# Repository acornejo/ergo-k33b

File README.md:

# ergo-k33b

A 56-key split/unified ortholinear keyboard with an integrated trackpad, designed in [Ergogen](https://ergogen.xyz/) and routed manually in KiCad.

## Overview

The ergo-k33b is a custom keyboard PCB featuring a symmetric 6×4 column-staggered matrix on each half, palm modifier keys, a 3-key thumb cluster per side, and an optional 65mm×50mm Azoteq TPS65 trackpad mounted in the center of the board.

The board uses a single unified PCB that mirrors the left and right halves — no split cable required.

## Images

### PCB — Top

### PCB — Bottom

### Front Plate

### Back Plate

### Case

## Key Layout

- **Total keys:** 56 (10 palm keys + 6 thumb keys + 40 matrix keys)
- **Matrix:** 6 columns × 4 rows per side, with column stagger:
  - Outer/pinky columns: +0/+2.5 mm stagger
  - Ring column: +5 mm stagger
  - Middle column: +2.5 mm stagger
  - Index column: −2.5 mm stagger
  - Inner column: −5 mm stagger
- **Thumb cluster:** 3 keys per side, splayed outward from the inner-bottom matrix position
- **Palm keys:** 1 key per side below the outer column, intended for modifier keys
- **Switch type:** Cherry MX (5-pin), with optional hotswap socket support

## Hardware

| Component | Part | Notes |
|---|---|---|
| MCU | [Nice!Nano](https://nicekeyboards.com/nice-nano/) (nRF52840 SuperMini) | Mounted on the back, centered between halves |
| Display | [Nice!View](https://nicekeyboards.com/nice-view/) | Optional; SPI via P1/P2/P3 |
| Trackpad | [Azoteq TPS65](https://www.azoteq.com/) (65mm × 50mm) | Optional; I²C via P4/P5, ready signal P0 |
| Switches | Cherry MX 5-pin | Hotswap and solder options |
| Diodes | SOD-123 (SMD) + THT | Both footprints populated; one per key |
| Battery connector | Molex Pico EZmate 1×2 | Also exposes BAT\_P / GND solder pads as an alternative |
| Trackpad connector | Molex Pico EZmate 1×5 | Also exposes RST / RDY / GND / VCC / SCL / SDA solder pads as an alternative |
| Power switch | SMD side-mount | On the back of the board |
| Reset button | SMD side-mount | On the back of the board |

### Connector choice

Both the battery and trackpad use [Molex Pico EZmate](https://www.molex.com/en-us/products/connectors/wire-to-board-connectors/pico-ezmate-connectors) connectors rather than the more common JST-PH standard. Pico EZmate has a lower profile (1.48 mm mated height vs. 3.0 mm for JST-PH), which keeps the overall board assembly thinner. Each connector also has corresponding solder pad footprints on the PCB, so you can wire the battery or trackpad directly without a connector if preferred.

## PCB Design

The PCB was designed using [Ergogen](https://ergogen.xyz/) v4.2 to generate the board outline, key positions, and component footprints from `ergogen/config.yaml`. Routing was done manually in KiCad. The freerouting scripts in this repo are provided for experimentation only.

Three PCBs are generated from the Ergogen config:

| PCB | Description |
|---|---|
| `main_board` | The keyboard PCB with all switches, diodes, MCU, and connectors |
| `frontplate` | Switch plate with key cutouts and screw holes |
| `backplate` | Bottom cover plate with screw holes |

A `bottom_case` 3D model (STL) is also generated from the Ergogen outlines using OpenJSCAD.

### Pinout (nRF52840 SuperMini)

| Pin | Function |
|---|---|
| P21 | Column: outer |
| P20 | Column: pinky |
| P19 | Column: ring |
| P18 | Column: middle |
| P15 | Column: index |
| P14 | Column: inner |
| P10 | Row: bottom |
| P8 | Row: home |
| P16 | Row: top |
| P7 | Row: num |
| P9 | Row: thumb cluster |
| P13 | Row: palm keys |
| P0 | Trackpad RDY |
| P4 | Trackpad SCL (I²C) |
| P5 | Trackpad SDA (I²C) |
| P6 | Trackpad RST |
| P1 | Nice!View CS |
| P2 | Nice!View MOSI |
| P3 | Nice!View SCK |

## Repository Structure

```
ergogen/
  config.yaml       # Full Ergogen board definition
output/
  pcbs/             # Generated KiCad PCB files
  cases/            # Generated OpenJSCAD and STL files
  outlines/         # Generated outline DXFs
  gerbers/          # Fabrication outputs
scripts/
  boards.kibot.yaml # KiBot config for main board exports
  default.kibot.yaml# KiBot config for plate exports
  export_dsn.py     # Export KiCad PCB to Specctra DSN
  import_ses.py     # Import Specctra SES back to KiCad
  freerouting.rules # Freerouting design rules
main_board.kicad_pcb # Hand-routed main board (source of truth)
build.sh            # Docker-based build script (KiBot + Freerouting)
images/             # Board renders
```

## Building

### Prerequisites

- [Node.js](https://nodejs.org/) (for Ergogen and OpenJSCAD CLI)
- [Docker](https://www.docker.com/) (for KiBot and Freerouting via containers)

### Generate PCB and case files from Ergogen

```bash
npm install
npm run build
```

This runs Ergogen to regenerate all PCBs, outlines, and case STL files under `output/`.

### Export Gerbers and run autorouting

```bash
./build.sh
```

This uses Docker to:
1. Run [KiBot](https://github.com/INTI-CMNB/KiBot) to export Gerbers for plates and boards
2. Export the board to Specctra DSN format
3. Autoroute with [Freerouting](https://github.com/freerouting/freerouting) (25 passes)
4. Import the routed SES back to KiCad and re-export Gerbers

> **Note:** The hand-routed `main_board.kicad_pcb` at the repo root is the production board. The autorouted output is for experimentation only.

### Clean generated output

```bash
npm run clean
```

## Firmware

The Nice!Nano runs [ZMK Firmware](https://zmk.dev/). Create a ZMK config repo with a shield definition matching the matrix pinout above.

## License

See [LICENSE](LICENSE).

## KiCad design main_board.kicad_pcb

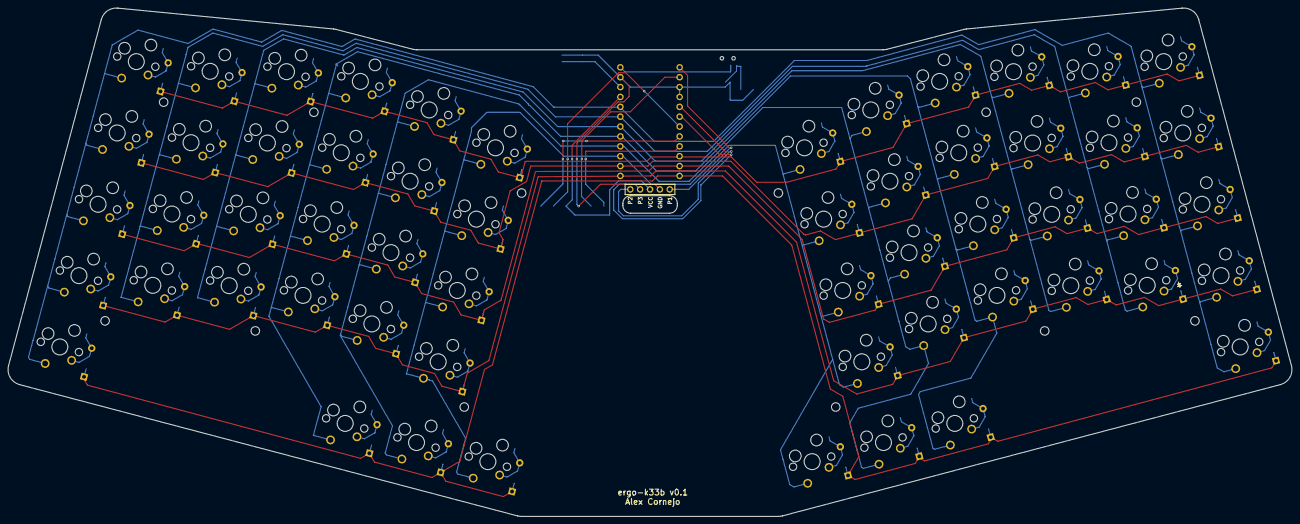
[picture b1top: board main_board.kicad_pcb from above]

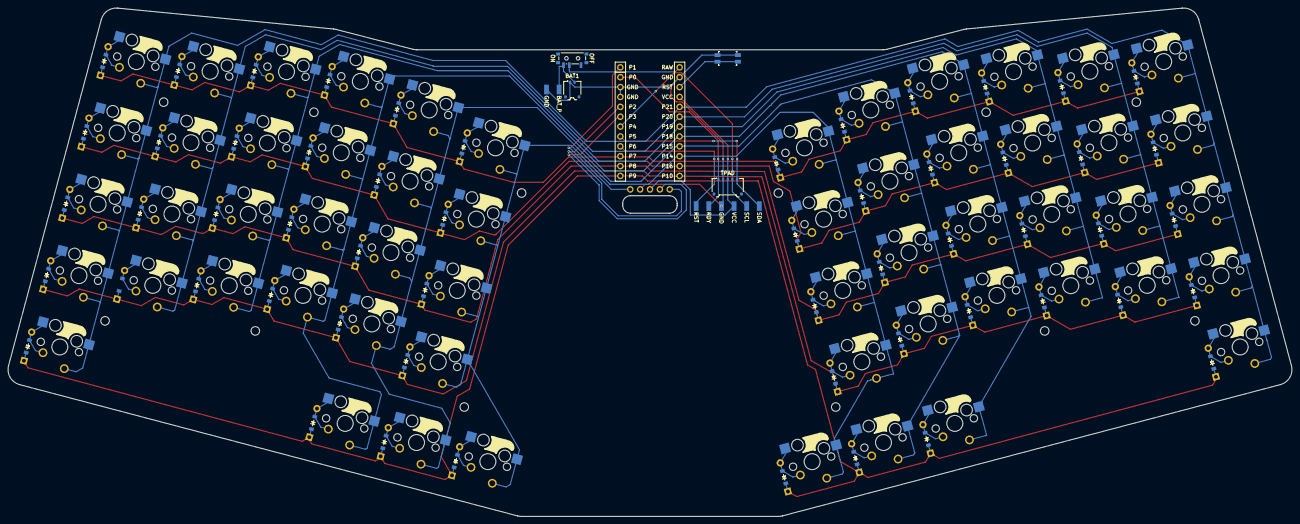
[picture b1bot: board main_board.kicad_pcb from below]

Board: 2 copper layers, 330.3 x 130.8 mm, 132 parts (116 on the bottom side), 79 nets.

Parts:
BAT1: Molex_Pico-EZmate_78171-0002_1x02-1MP_P1.20mm_Vertical
BAT_PADS1: pads
D1, D2, D3, D4, D5, D6, D7, D8, D9, D10, D11, D12, D13, D14, D15, D16, D17, D18, D19, D20, D21, D22, D23, D24, D25, D26, D27, D28, D29, D30, D31, D32, D33, D34, D35, D36, D37, D38, D39, D40, D41, D42, D43, D44, D45, D46, D47, D48, D49, D50, D51, D52, D53, D54, D55, D56: diode_tht_sod123
DISP1: display_nice_view
MCU1: mcu_supermini_nrf52840
MH1, MH2, MH3, MH4, MH5, MH6, MH7, MH8, MH9, MH10, MH11, MH12: mounting_hole_npth
PWR1: power_switch_smd_side
RST1: reset_switch_smd_side
S1, S2, S3, S4, S5, S6, S7, S8, S9, S10, S11, S12, S13, S14, S15, S16, S17, S18, S19, S20, S21, S22, S23, S24, S25, S26, S27, S28: switch_mx
S29, S30, S31, S32, S33, S34, S35, S36, S37, S38, S39, S40, S41, S42, S43, S44, S45, S46, S47, S48, S49, S50, S51, S52, S53, S54, S55, S56: switch_mx2
TPAD: Molex_Pico-EZmate_78171-0005_1x05-1MP_P1.20mm_Vertical
TPAD_PADS1: pads

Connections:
BAT_P: BAT1.2, BAT_PADS1.1, PWR1.3
GND: BAT1.1, BAT_PADS1.2, DISP1.4, MCU1.3, MCU1.4, MCU1.23, RST1.1, RST1.3, TPAD.2, TPAD_PADS1.4
P0: MCU1.2, TPAD.1, TPAD_PADS1.5
P1: DISP1.5, MCU1.1
P2: DISP1.1, MCU1.5
P3: DISP1.2, MCU1.6
P4: MCU1.7, TPAD.4, TPAD_PADS1.2
P5: MCU1.8, TPAD.5, TPAD_PADS1.1
P6: MCU1.9, TPAD_PADS1.6
P7: D4.1, D8.1, D12.1, D16.1, D20.1, D24.1, D32.1, D36.1, D40.1, D44.1, D48.1, D52.1, MCU1.10
P8: D2.1, D6.1, D10.1, D14.1, D18.1, D22.1, D30.1, D34.1, D38.1, D42.1, D46.1, D50.1, MCU1.11
P9: D25.1, D26.1, D27.1, D28.1, D53.1, D54.1, D55.1, D56.1, MCU1.12
P10: D1.1, D5.1, D9.1, D13.1, D17.1, D21.1, D29.1, D33.1, D37.1, D41.1, D45.1, D49.1, MCU1.13
P14: MCU1.20, S1.1, S2.1, S3.1, S4.1, S28.1, S29.1, S30.1, S31.1, S32.1, S56.1
P15: MCU1.19, S5.1, S6.1, S7.1, S8.1, S33.1, S34.1, S35.1, S36.1
P16: D3.1, D7.1, D11.1, D15.1, D19.1, D23.1, D31.1, D35.1, D39.1, D43.1, D47.1, D51.1, MCU1.14
P18: MCU1.18, S9.1, S10.1, S11.1, S12.1, S37.1, S38.1, S39.1, S40.1
P19: MCU1.17, S13.1, S14.1, S15.1, S16.1, S25.1, S41.1, S42.1, S43.1, S44.1, S53.1
P20: MCU1.16, S17.1, S18.1, S19.1, S20.1, S26.1, S45.1, S46.1, S47.1, S48.1, S54.1
P21: MCU1.15, S21.1, S22.1, S23.1, S24.1, S27.1, S49.1, S50.1, S51.1, S52.1, S55.1
RAW: MCU1.24, PWR1.2
RST: MCU1.22, RST1.2, RST1.4
VCC: DISP1.3, MCU1.21, TPAD.3, TPAD_PADS1.3
far_cluster: D27.2, S27.2
home_cluster: D26.2, S26.2
index_bottom: D17.2, S17.2
index_home: D18.2, S18.2
index_num: D20.2, S20.2
index_top: D19.2, S19.2
inner_bottom: D21.2, S21.2
inner_home: D22.2, S22.2
inner_num: D24.2, S24.2
inner_top: D23.2, S23.2
middle_bottom: D13.2, S13.2
middle_home: D14.2, S14.2
middle_num: D16.2, S16.2
middle_top: D15.2, S15.2
mirror_far_cluster: D55.2, S55.2
mirror_home_cluster: D54.2, S54.2
mirror_index_bottom: D45.2, S45.2
mirror_index_home: D46.2, S46.2
mirror_index_num: D48.2, S48.2
mirror_index_top: D47.2, S47.2
mirror_inner_bottom: D49.2, S49.2
mirror_inner_home: D50.2, S50.2
mirror_inner_num: D52.2, S52.2
mirror_inner_top: D51.2, S51.2
mirror_middle_bottom: D41.2, S41.2
mirror_middle_home: D42.2, S42.2
mirror_middle_num: D44.2, S44.2
mirror_middle_top: D43.2, S43.2
mirror_near_cluster: D53.2, S53.2
mirror_outer_bottom: D29.2, S29.2
mirror_outer_home: D30.2, S30.2
mirror_outer_num: D32.2, S32.2
mirror_outer_top: D31.2, S31.2
mirror_pinky_bottom: D33.2, S33.2
mirror_pinky_home: D34.2, S34.2
mirror_pinky_num: D36.2, S36.2
mirror_pinky_top: D35.2, S35.2
mirror_ring_bottom: D37.2, S37.2
mirror_ring_home: D38.2, S38.2
mirror_ring_num: D40.2, S40.2
mirror_ring_top: D39.2, S39.2
mirror_single_cluster: D56.2, S56.2
near_cluster: D25.2, S25.2
outer_bottom: D1.2, S1.2
outer_home: D2.2, S2.2
outer_num: D4.2, S4.2
outer_top: D3.2, S3.2
pinky_bottom: D5.2, S5.2
pinky_home: D6.2, S6.2
pinky_num: D8.2, S8.2
pinky_top: D7.2, S7.2
ring_bottom: D9.2, S9.2
ring_home: D10.2, S10.2
ring_num: D12.2, S12.2
ring_top: D11.2, S11.2
single_cluster: D28.2, S28.2

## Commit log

2026-06-10 update readme to include details on connectors.
